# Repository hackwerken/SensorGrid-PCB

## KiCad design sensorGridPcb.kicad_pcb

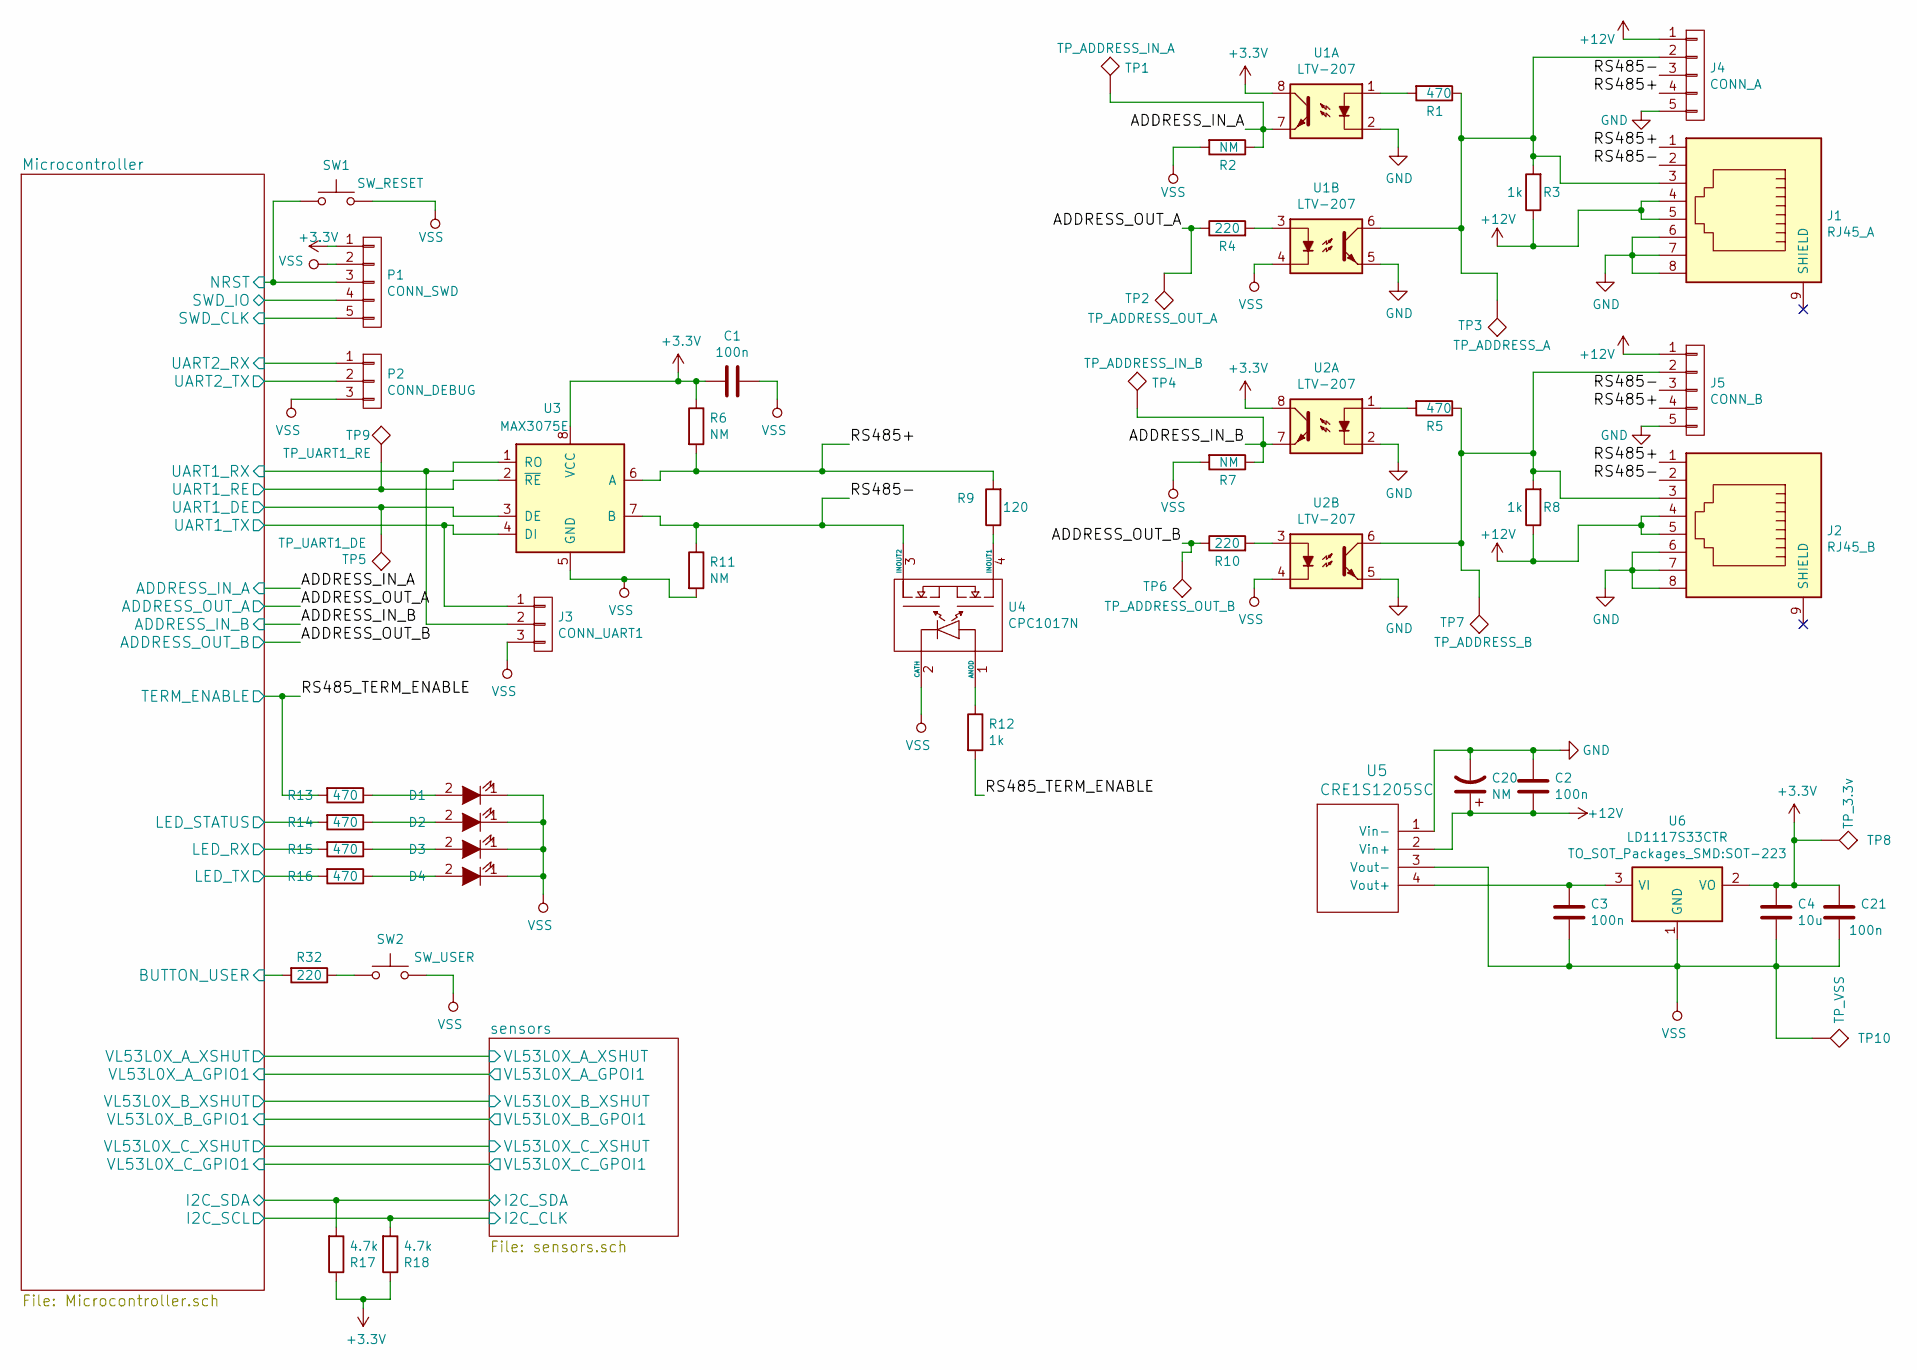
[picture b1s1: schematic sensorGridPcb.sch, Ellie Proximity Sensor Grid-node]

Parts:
C1, C2, C3: 100n; C_0805_HandSoldering
C4: 10u; C_0805_HandSoldering
C20: NM; CP_Elec_5x5.7
C21: 100n; C_0805
D1: TERM; LED_0805
D2: STAT; LED_0805
D3: RX; LED_0805
D4: TX; LED_0805
J1: RJ45_A; RJ45_8
J2: RJ45_B; RJ45_8
J3: CONN_UART1; Pin_Header_Straight_1x03_Pitch2.54mm
J4: CONN_A; Socket_Strip_Straight_1x05_Pitch2.54mm
J5: CONN_B; Socket_Strip_Straight_1x05_Pitch2.54mm
P1: CONN_SWD; Pin_Header_Straight_1x05
P2: CONN_DEBUG; Pin_Header_Straight_1x03
R1, R5, R13, R14, R15, R16: 470; R_0805_HandSoldering
R2, R6, R7, R11: NM; R_0805_HandSoldering
R3, R8, R12: 1k; R_0805_HandSoldering
R4, R10, R32: 220; R_0805_HandSoldering
R9: 120; R_1206_HandSoldering
R17, R18: 4.7k; R_0805_HandSoldering
SW1: SW_RESET; SW_PUSH_SMALL
SW2: SW_USER; SW_PUSH_SMALL
TP1: TP_ADDRESS_IN_A; Measurement_Point_Round-SMD-Pad_Small
TP2: TP_ADDRESS_OUT_A; Measurement_Point_Round-SMD-Pad_Small
TP3: TP_ADDRESS_A; Measurement_Point_Round-SMD-Pad_Small
TP4: TP_ADDRESS_IN_B; Measurement_Point_Round-SMD-Pad_Small
TP5: TP_UART1_DE; Measurement_Point_Round-SMD-Pad_Small
TP6: TP_ADDRESS_OUT_B; Measurement_Point_Round-SMD-Pad_Small
TP7: TP_ADDRESS_B; Measurement_Point_Round-SMD-Pad_Small
TP8: TP_3.3v; Measurement_Point_Round-SMD-Pad_Small
TP9: TP_UART1_RE; Measurement_Point_Round-SMD-Pad_Small
TP10: TP_VSS; Measurement_Point_Round-SMD-Pad_Small
U1, U2: LTV-207; SOP8
U3: MAX3075E; DIP-8_W7.62mm_Socket
U4: CPC1017N
U5: CRE1S1205SC; CRE1S
U6: LD1117S33CTR; SOT-223

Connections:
+3V3: C1.2, C4.1, C21.1, P1.1, R6.1, R17.1, R18.1, TP8.1, U1.8, U2.8, U3.8 (VCC), U6.2 (VO), U6.4; also elsewhere on the board
+12V: C2.2, C20.1, J1.4, J1.5, J2.4, J2.5, J4.1, J5.1, R3.1, R8.1, U5.2 (Vin+)
/ADDRESS_IN_A: R2.1, TP1.1, U1.7; also elsewhere on the board
/ADDRESS_IN_B: R7.1, TP4.1, U2.7; also elsewhere on the board
/ADDRESS_OUT_A: R4.1, TP2.1; also elsewhere on the board
/ADDRESS_OUT_B: R10.1, TP6.1; also elsewhere on the board
/Microcontroller/BUTTON_USER: R32.2; also elsewhere on the board
/Microcontroller/I2C_SDA: R17.2; also elsewhere on the board
/Microcontroller/LED_RX: R15.2; also elsewhere on the board
/Microcontroller/LED_STATUS: R14.2; also elsewhere on the board
/Microcontroller/LED_TX: R16.2; also elsewhere on the board
/Microcontroller/NRST: P1.3, SW1.1; also elsewhere on the board
/Microcontroller/SWD_CLK: P1.5; also elsewhere on the board
/Microcontroller/SWD_IO: P1.4; also elsewhere on the board
/Microcontroller/UART1_DE: TP5.1, U3.3 (DE); also elsewhere on the board
/Microcontroller/UART1_RE: TP9.1, U3.2 (~RE~); also elsewhere on the board
/Microcontroller/UART1_RX: J3.2, U3.1 (RO); also elsewhere on the board
/Microcontroller/UART1_TX: J3.1, U3.4 (DI); also elsewhere on the board
/Microcontroller/UART2_RX: P2.1; also elsewhere on the board
/Microcontroller/UART2_TX: P2.2; also elsewhere on the board
/RS485+: J1.1, J2.1, J4.4, J5.4, R6.2, R9.2, U3.6 (A)
/RS485-: J1.2, J2.2, J4.3, J5.3, R11.1, U3.7 (B), U4.3 (INOUT2)
/RS485_TERM_ENABLE: R12.2, R13.2; also elsewhere on the board
/sensors/I2C_CLK: R18.2; also elsewhere on the board
GND: C2.1, C20.2, J1.6, J1.7, J1.8, J2.6, J2.7, J2.8, J4.5, J5.5, U1.2, U1.5, U2.2, U2.5, U5.1 (Vin-)
unnamed: C3.1, U5.4 (Vout+), U6.3 (VI)
unnamed: D1.2 (A), R13.1
unnamed: D2.2 (A), R14.1
unnamed: D3.2 (A), R15.1
unnamed: D4.2 (A), R16.1
unnamed: J1.3, J4.2, R1.1, R3.2, TP3.1, U1.6
unnamed: J2.3, J5.2, R5.1, R8.2, TP7.1, U2.6
unnamed: R1.2, U1.1
unnamed: R4.2, U1.3
unnamed: R5.2, U2.1
unnamed: R9.1, U4.4 (INOUT1)
unnamed: R10.2, U2.3
unnamed: R12.1, U4.1 (ANOD)
unnamed: R32.1, SW2.1
VSS: C1.1, C3.2, C4.2, C21.2, D1.1 (K), D2.1 (K), D3.1 (K), D4.1 (K), J3.3, P1.2, P2.3, R2.2, R7.2, R11.2, SW1.2, SW2.2, TP10.1, U1.4, U2.4, U3.5 (GND), U4.2 (CATH), U5.3 (Vout-), U6.1 (GND); also elsewhere on the board

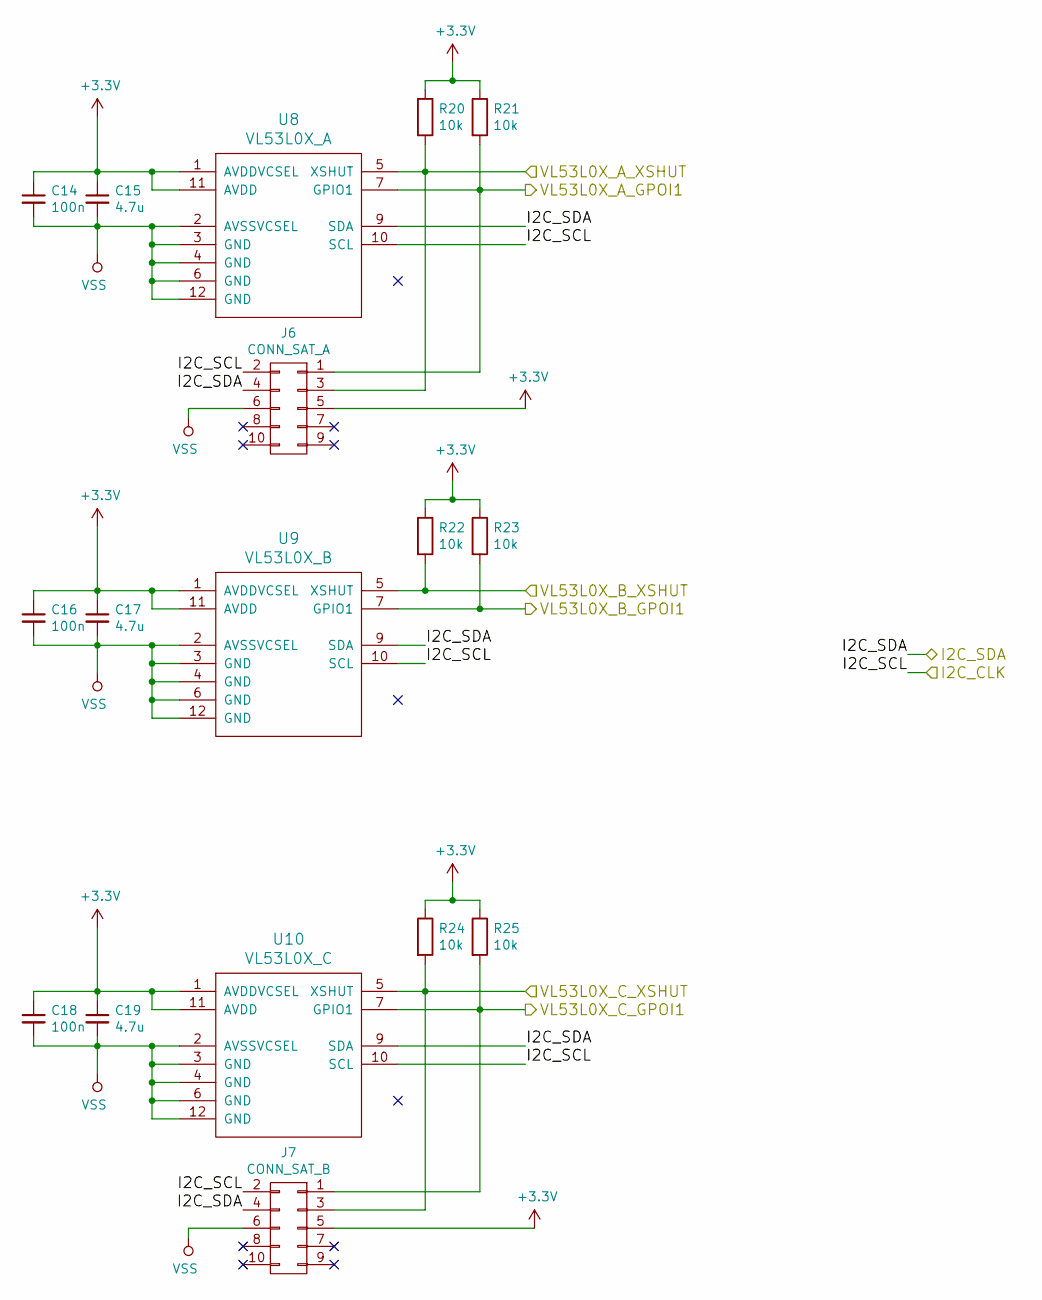
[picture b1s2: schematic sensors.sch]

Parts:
C14, C16, C18: 100n; C_0805_HandSoldering
C15, C17, C19: 4.7u; C_0805_HandSoldering
J6: CONN_SAT_A; Pin_Header_Straight_2x05_Pitch2.54mm
J7: CONN_SAT_B; Pin_Header_Straight_2x05_Pitch2.54mm
R20, R21, R22, R23, R24, R25: 10k; R_0805_HandSoldering
U8: VL53L0X_A; VL53L0X
U9: VL53L0X_B; VL53L0X
U10: VL53L0X_C; VL53L0X

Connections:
+3V3: C14.1, C15.1, C16.1, C17.1, C18.1, C19.1, J6.5, J7.5, R20.1, R21.1, R22.1, R23.1, R24.1, R25.1, U8.1 (AVDDVCSEL), U8.11 (AVDD), U9.1 (AVDDVCSEL), U9.11 (AVDD), U10.1 (AVDDVCSEL), U10.11 (AVDD); also elsewhere on the board
/Microcontroller/I2C_SDA: J6.4, J7.4, U8.9 (SDA), U9.9 (SDA), U10.9 (SDA); also elsewhere on the board
/Microcontroller/VL53L0X_A_GPIO1: J6.1, R21.2, U8.7 (GPIO1); also elsewhere on the board
/Microcontroller/VL53L0X_A_XSHUT: J6.3, R20.2, U8.5 (XSHUT); also elsewhere on the board
/Microcontroller/VL53L0X_B_GPIO1: R23.2, U9.7 (GPIO1); also elsewhere on the board
/Microcontroller/VL53L0X_B_XSHUT: R22.2, U9.5 (XSHUT); also elsewhere on the board
/Microcontroller/VL53L0X_C_GPIO1: J7.1, R25.2, U10.7 (GPIO1); also elsewhere on the board
/Microcontroller/VL53L0X_C_XSHUT: J7.3, R24.2, U10.5 (XSHUT); also elsewhere on the board
/sensors/I2C_CLK: J6.2, J7.2, U8.10 (SCL), U9.10 (SCL), U10.10 (SCL); also elsewhere on the board
VSS: C14.2, C15.2, C16.2, C17.2, C18.2, C19.2, J6.6, J7.6, U8.2 (AVSSVCSEL), U8.3 (GND), U8.4 (GND), U8.6 (GND), U8.12 (GND), U9.2 (AVSSVCSEL), U9.3 (GND), U9.4 (GND), U9.6 (GND), U9.12 (GND), U10.2 (AVSSVCSEL), U10.3 (GND), U10.4 (GND), U10.6 (GND), U10.12 (GND); also elsewhere on the board

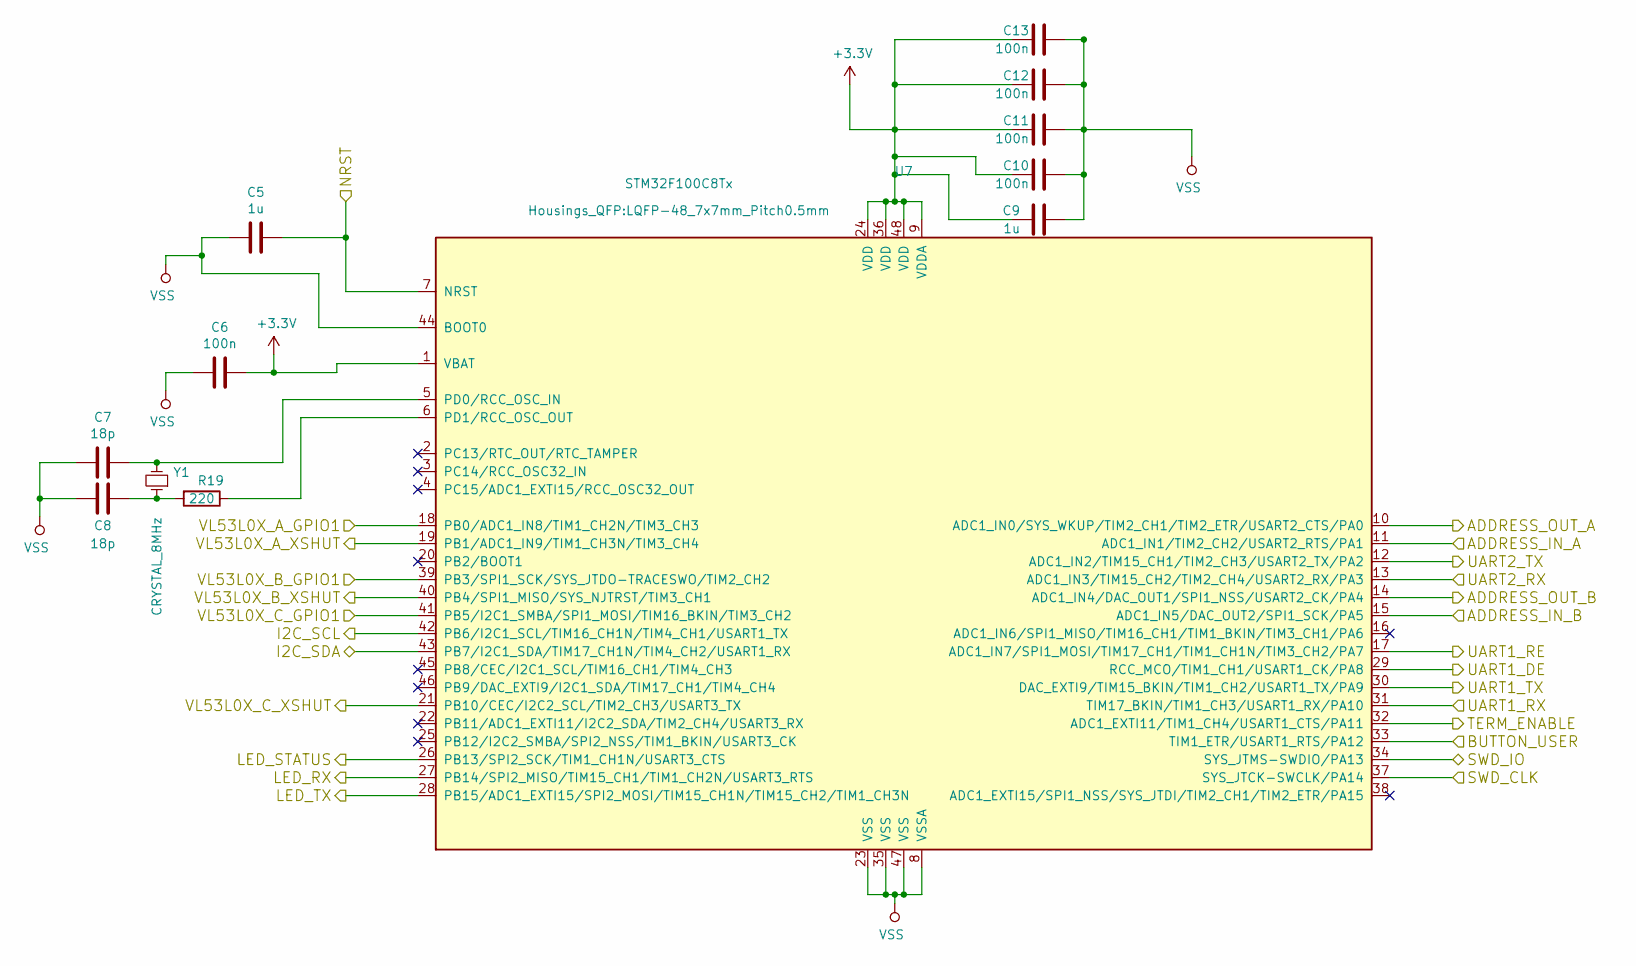
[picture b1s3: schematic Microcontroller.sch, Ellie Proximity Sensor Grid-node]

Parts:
C5, C9: 1u; C_0805_HandSoldering
C6, C10, C11, C12, C13: 100n; C_0805_HandSoldering
C7, C8: 18p; C_0805_HandSoldering
R19: 220; R_0805_HandSoldering
U7: STM32F100C8Tx; LQFP-48_7x7mm_Pitch0.5mm
Y1: CRYSTAL_8MHz; Crystal_HC49-U_Vertical

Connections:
+3V3: C6.1, C9.1, C10.1, C11.1, C12.1, C13.1, U7.1 (VBAT), U7.9 (VDDA), U7.24 (VDD), U7.36 (VDD), U7.48 (VDD); also elsewhere on the board
/ADDRESS_IN_A: U7.11 (ADC1_IN1/TIM2_CH2/USART2_RTS/PA1); also elsewhere on the board
/ADDRESS_IN_B: U7.15 (ADC1_IN5/DAC_OUT2/SPI1_SCK/PA5); also elsewhere on the board
/ADDRESS_OUT_A: U7.10 (ADC1_IN0/SYS_WKUP/TIM2_CH1/TIM2_ETR/USA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); also elsewhere on the board
/ADDRESS_OUT_B: U7.14 (ADC1_IN4/DAC_OUT1/SPI1_NSS/USART2_CK/PA4); also elsewhere on the board
/Microcontroller/BUTTON_USER: U7.33 (TIM1_ETR/USART1_RTS/PA12); also elsewhere on the board
/Microcontroller/I2C_SDA: U7.43 (PB7/I2C1_SDA/TIM17_CH1N/TIM4_CH2/USART1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); also elsewhere on the board
/Microcontroller/LED_RX: U7.27 (PB14/SPI2_MISO/TIM15_CH1/TIM1_CH2N/USAR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); also elsewhere on the board
/Microcontroller/LED_STATUS: U7.26 (PB13/SPI2_SCK/TIM1_CH1N/USART3_CTS); also elsewhere on the board
/Microcontroller/LED_TX: U7.28 (PB15/ADC1_EXTI15/SPI2_MOSI/TIM15_CH1N/T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); also elsewhere on the board
/Microcontroller/NRST: C5.1, U7.7 (NRST); also elsewhere on the board
/Microcontroller/SWD_CLK: U7.37 (SYS_JTCK-SWCLK/PA14); also elsewhere on the board
/Microcontroller/SWD_IO: U7.34 (SYS_JTMS-SWDIO/PA13); also elsewhere on the board
/Microcontroller/UART1_DE: U7.29 (RCC_MCO/TIM1_CH1/USART1_CK/PA8); also elsewhere on the board
/Microcontroller/UART1_RE: U7.17 (ADC1_IN7/SPI1_MOSI/TIM17_CH1/TIM1_CH1N/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); also elsewhere on the board
/Microcontroller/UART1_RX: U7.31 (TIM17_BKIN/TIM1_CH3/USART1_RX/PA10); also elsewhere on the board
/Microcontroller/UART1_TX: U7.30 (DAC_EXTI9/TIM15_BKIN/TIM1_CH2/USART1_TX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); also elsewhere on the board
/Microcontroller/UART2_RX: U7.13 (ADC1_IN3/TIM15_CH2/TIM2_CH4/USART2_RX/P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); also elsewhere on the board
/Microcontroller/UART2_TX: U7.12 (ADC1_IN2/TIM15_CH1/TIM2_CH3/USART2_TX/P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); also elsewhere on the board
/Microcontroller/VL53L0X_A_GPIO1: U7.18 (PB0/ADC1_IN8/TIM1_CH2N/TIM3_CH3); also elsewhere on the board
/Microcontroller/VL53L0X_A_XSHUT: U7.19 (PB1/ADC1_IN9/TIM1_CH3N/TIM3_CH4); also elsewhere on the board
/Microcontroller/VL53L0X_B_GPIO1: U7.39 (PB3/SPI1_SCK/SYS_JTDO-TRACESWO/TIM2_CH2); also elsewhere on the board
/Microcontroller/VL53L0X_B_XSHUT: U7.40 (PB4/SPI1_MISO/SYS_NJTRST/TIM3_CH1); also elsewhere on the board
/Microcontroller/VL53L0X_C_GPIO1: U7.41 (PB5/I2C1_SMBA/SPI1_MOSI/TIM16_BKIN/TIM3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); also elsewhere on the board
/Microcontroller/VL53L0X_C_XSHUT: U7.21 (PB10/CEC/I2C2_SCL/TIM2_CH3/USART3_TX); also elsewhere on the board
/RS485_TERM_ENABLE: U7.32 (ADC1_EXTI11/TIM1_CH4/USART1_CTS/PA11); also elsewhere on the board
/sensors/I2C_CLK: U7.42 (PB6/I2C1_SCL/TIM16_CH1N/TIM4_CH1/USART1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); also elsewhere on the board
unnamed: C7.2, U7.5 (PD0/RCC_OSC_IN), Y1.2
unnamed: C8.2, R19.2, Y1.1
unnamed: R19.1, U7.6 (PD1/RCC_OSC_OUT)
VSS: C5.2, C6.2, C7.1, C8.1, C9.2, C10.2, C11.2, C12.2, C13.2, U7.8 (VSSA), U7.23 (VSS), U7.35 (VSS), U7.44 (BOOT0), U7.47 (VSS); also elsewhere on the board

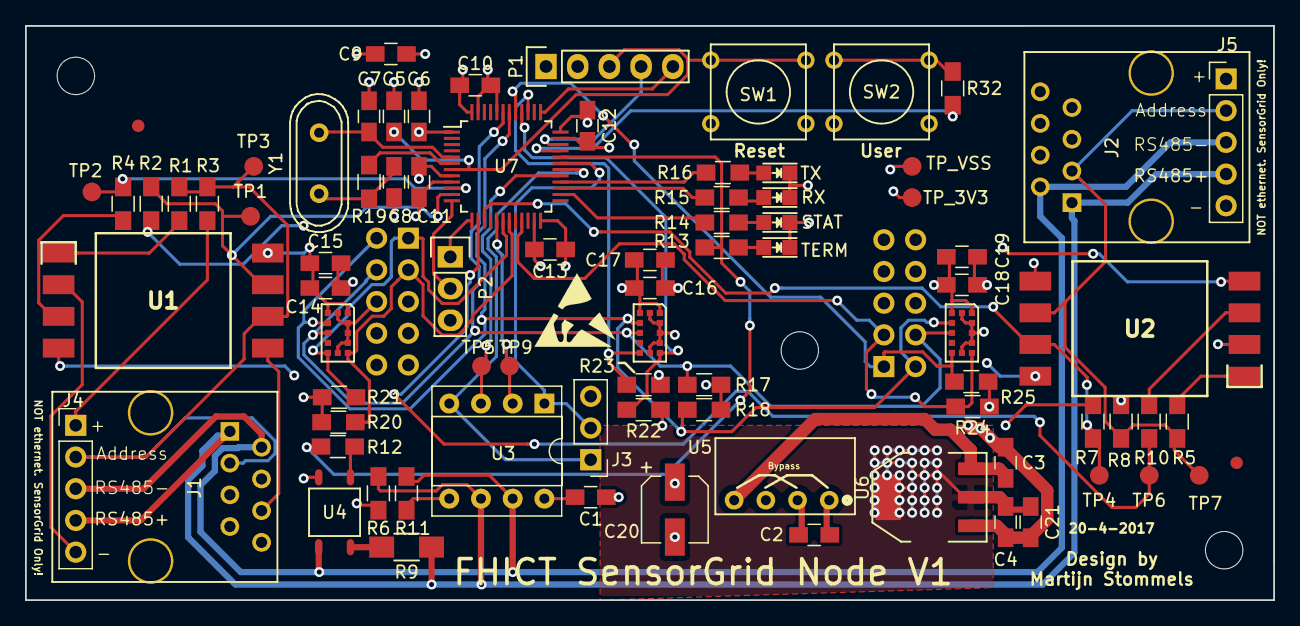
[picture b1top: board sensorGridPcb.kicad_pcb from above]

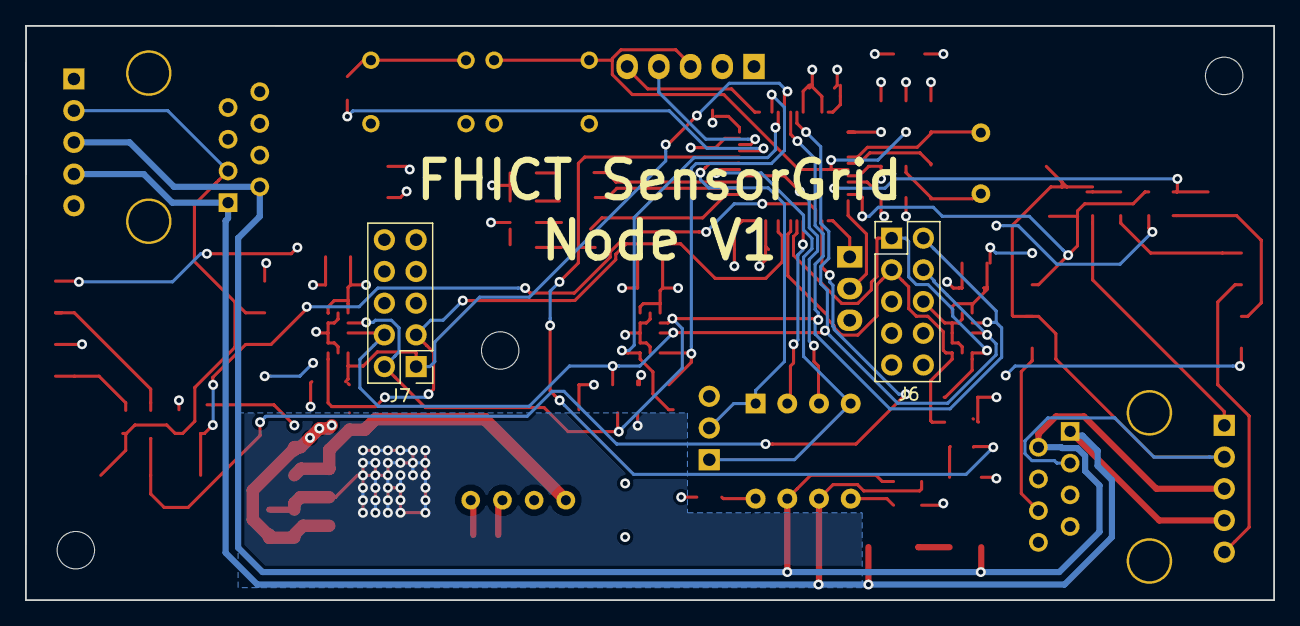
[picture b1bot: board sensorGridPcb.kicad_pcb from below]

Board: 4 copper layers, 100.0 x 46.0 mm, 83 parts (2 on the bottom side), 49 nets.

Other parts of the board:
TP_3V3: TP_3.3v; Measurement_Point_Round-SMD-Pad_Small
TP_VSS: TP_VSS; Measurement_Point_Round-SMD-Pad_Small

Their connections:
+3V3: TP_3V3.1; also elsewhere on the board
VSS: TP_VSS.1; also elsewhere on the board

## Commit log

2016-12-01 Rev 1.
2017-04-21 Finished rev4
2017-05-19 Added pdf exports of the schematic and pcb.
